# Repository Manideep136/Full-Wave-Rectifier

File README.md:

# Full-Wave-Rectifier
Project Overview

This project is a Full Wave Rectifier designed using KiCad. A full wave rectifier converts an AC (Alternating Current) input into a pulsating DC (Direct Current) output by using both the positive and negative half cycles of the AC waveform.

Unlike a half-wave rectifier, which uses only one half cycle of the AC signal, a full wave rectifier provides a more efficient conversion because both halves of the AC waveform are utilized.

This project can be used as a basic electronics learning project to understand AC-to-DC conversion, diode rectification, filtering, and PCB design.

🎯 Objectives
Convert AC voltage into DC voltage.
Understand the working of a full wave rectifier.
Learn how diodes are used for rectification.
Reduce output voltage ripple using a capacitor.
Design the complete circuit using KiCad.
Create the schematic and PCB layout.
Practice footprint assignment, PCB routing, ERC, and DRC.
⚙️ Working Principle

The circuit uses four diodes connected in a bridge configuration, commonly called a Full Wave Bridge Rectifier.

During the positive half cycle of the AC input, two diodes conduct and allow current to flow through the load in one direction.

During the negative half cycle, the other two diodes conduct. Although the AC input polarity has reversed, the current through the load still flows in the same direction.

Therefore, both half cycles are converted into pulsating DC.

A capacitor can be connected across the output to smooth the pulsating DC and obtain a more stable DC voltage.

✅ Advantages
Uses both halves of the AC waveform.
Higher efficiency than a half-wave rectifier.
Produces lower ripple compared with a half-wave rectifier.
Does not require a center-tapped transformer.
Simple and widely used circuit.
Suitable for basic AC-to-DC power supplies.
⚠️ Limitations
Four diodes are required.
Current passes through two diodes during each half cycle.
Therefore, there is a forward voltage drop across two diodes.
Output still contains ripple without a filter capacitor.
The diode ratings must be selected according to the input voltage and load current.
🔍 Testing

After completing the PCB design:

Check the schematic connections.
Verify diode orientation.
Check capacitor polarity.
Assign the correct footprints.
Run ERC.
Correct any ERC errors.
Update the PCB.
Place the components.
Route the tracks.
Run DRC.
Inspect the PCB using the 3D Viewer.

For practical testing, use a safe low-voltage AC source appropriate for the component ratings.

🛡️ Safety

⚠️ Do not connect the circuit directly to 230 V AC mains unless the entire design is specifically rated and designed for mains voltage.

For a beginner project, use a low-voltage isolated AC source or transformer secondary.

Important considerations include:

Correct diode voltage and current ratings.
Correct capacitor voltage rating.
Proper PCB clearance and creepage.
Correct polarity of electrolytic capacitors.
Proper fuse and protection where required.
Never touch exposed mains-voltage circuitry while powered.
🚀 Future Improvements

The project can be improved by adding:

Voltage regulator such as 7805.
Larger filter capacitor for lower ripple.
LED power indicator.
Fuse and protection circuit.
Screw-terminal connectors.
Adjustable voltage regulator.
PCB test points.
Reverse-polarity protection.
Complete regulated DC power supply.
📚 Learning Outcomes

By completing this project, you can learn:

AC-to-DC conversion.
Full-wave bridge rectification.
Diode operation.
Capacitor filtering.
Ripple voltage.
Schematic design in KiCad.
Footprint assignment.
PCB layout and routing.
ERC and DRC.
PCB 3D visualization.
👨‍💻 Software

KiCad 9.0

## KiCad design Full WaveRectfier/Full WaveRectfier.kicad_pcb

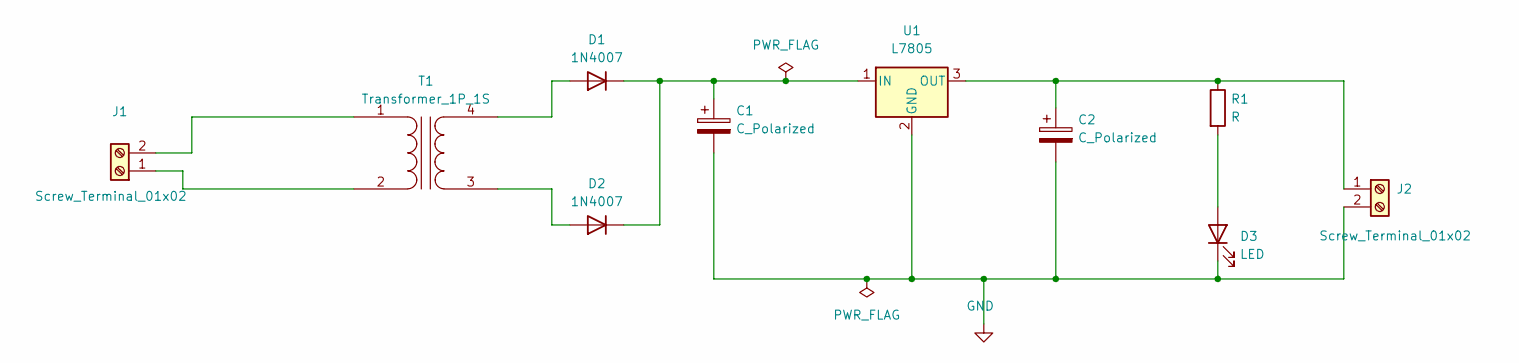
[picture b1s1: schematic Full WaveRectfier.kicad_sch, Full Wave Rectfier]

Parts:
C1, C2: C_Polarized; C_Radial_D5.0mm_H11.0mm_P2.00mm
D1, D2: 1N4007; D_DO-41_SOD81_P10.16mm_Horizontal
D3: LED; LED_D5.0mm
J1, J2: Screw_Terminal_01x02; TerminalBlock_Phoenix_MKDS-1,5-2_1x02_P5.00mm_Horizontal
R1: R; R_Axial_DIN0414_L11.9mm_D4.5mm_P15.24mm_Horizontal
T1: Transformer_1P_1S; Transformer_Zeming_ZMPT101K
U1: L7805; TO-220-3_Vertical

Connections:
GND: C1.2, C2.2, D3.1 (K), J2.2, U1.2 (GND)
unnamed: D1.2 (A), T1.4 (SB)
unnamed: C1.1, D1.1 (K), D2.1 (K), U1.1 (IN)
unnamed: D2.2 (A), T1.3 (SA)
unnamed: D3.2 (A), R1.2
unnamed: J1.1, T1.2 (AB)
unnamed: J1.2, T1.1 (AA)
unnamed: C2.1, J2.1, R1.1, U1.3 (OUT)

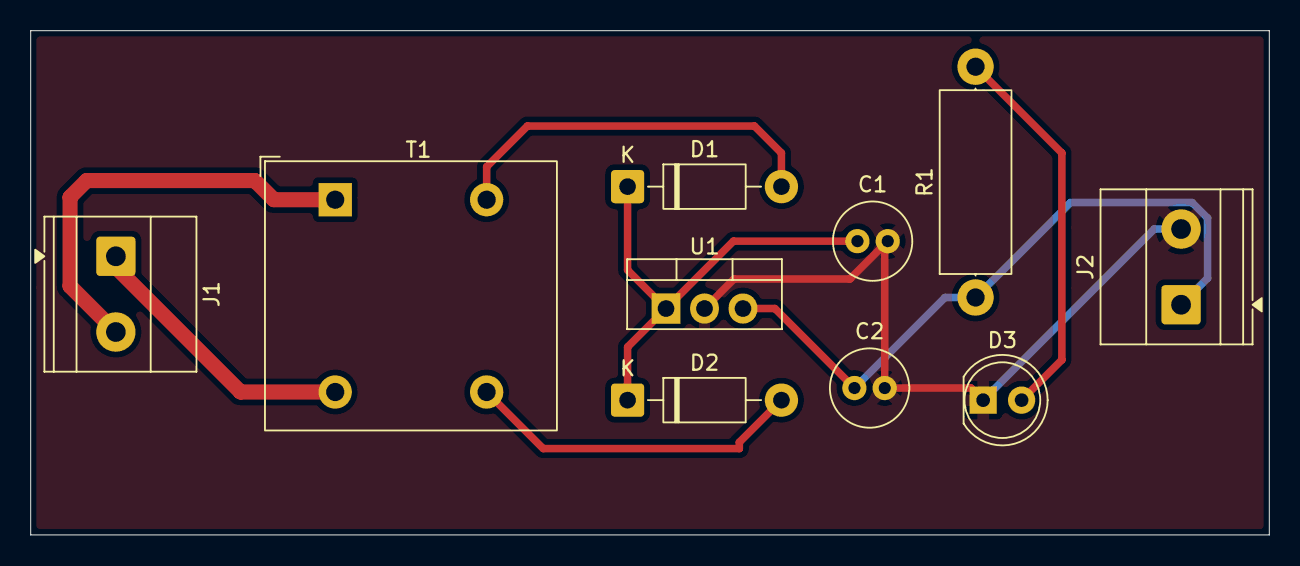
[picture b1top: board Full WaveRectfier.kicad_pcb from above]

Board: 2 copper layers, 81.8 x 33.3 mm, 10 parts (0 on the bottom side), 8 nets.
